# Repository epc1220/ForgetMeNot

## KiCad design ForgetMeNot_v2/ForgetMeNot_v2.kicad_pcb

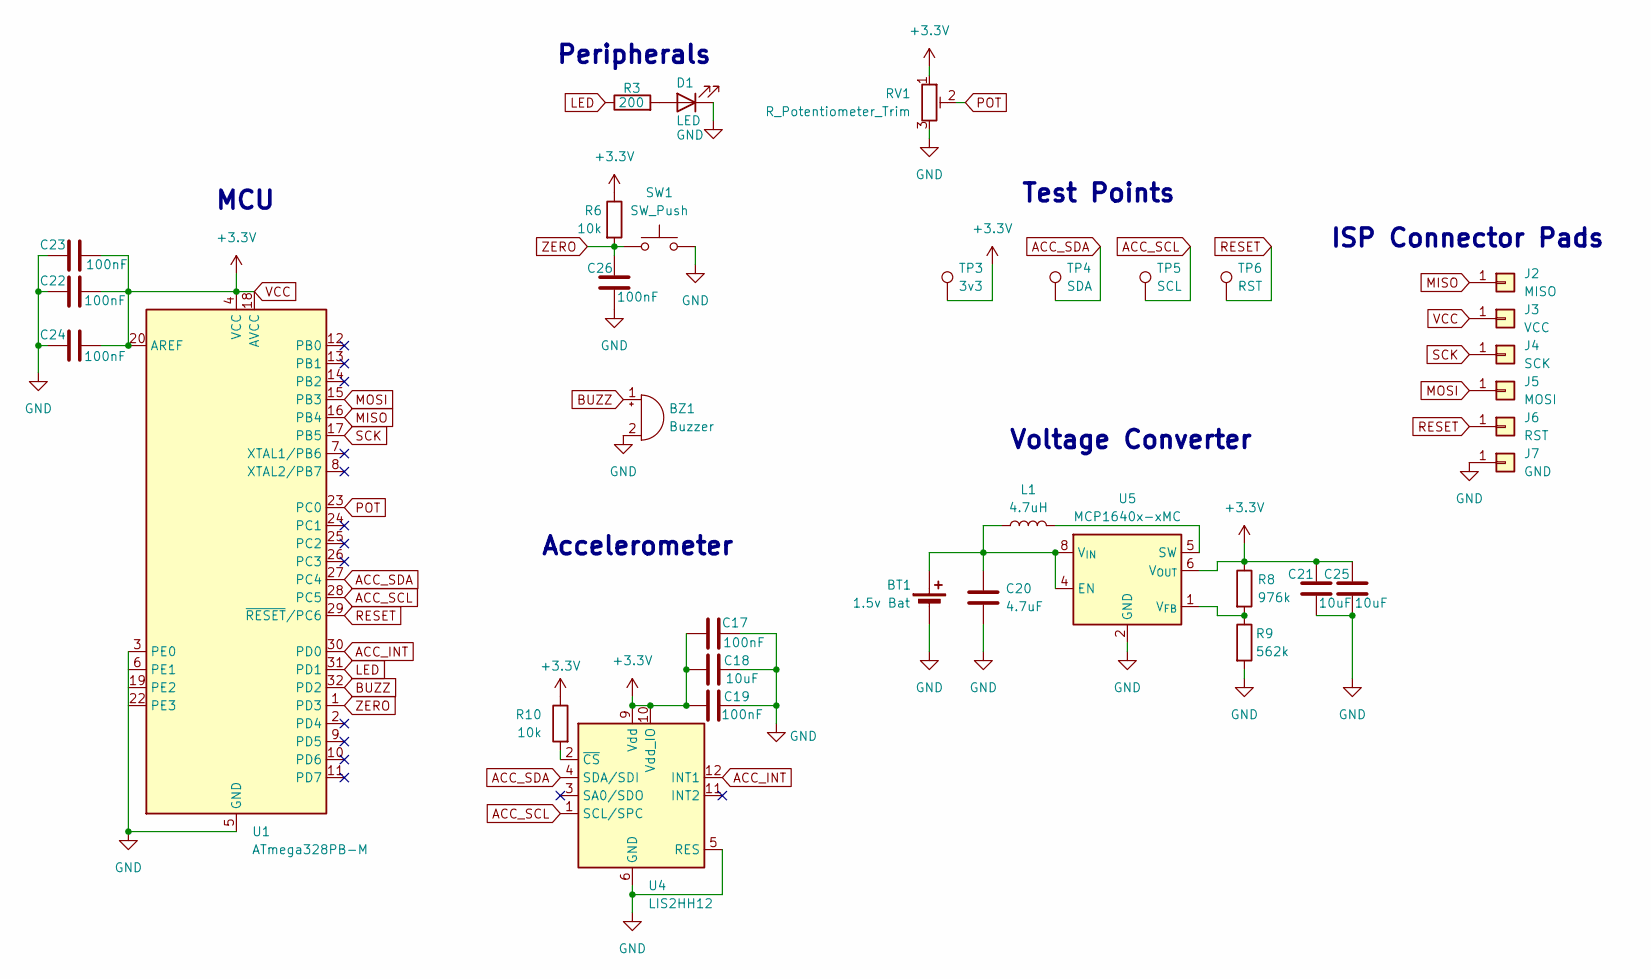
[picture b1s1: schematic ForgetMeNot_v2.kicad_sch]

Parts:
BT1: 1.5v Bat; BatteryHolder_Keystone_2998_1x6.8mm
BZ1: Buzzer; Buzzer_CUI_CPT-9019S-SMT
C17, C19, C22, C23, C24, C26: 100nF; C_0402_1005Metric
C18, C21, C25: 10uF; C_0402_1005Metric
C20: 4.7uF; C_0402_1005Metric
D1: LED; LED_0402_1005Metric
J2: MISO; SolderWirePad_1x01_SMD_3x6mm
J3: VCC; SolderWirePad_1x01_SMD_3x6mm
J4: SCK; SolderWirePad_1x01_SMD_3x6mm
J5: MOSI; SolderWirePad_1x01_SMD_3x6mm
J6: RST; SolderWirePad_1x01_SMD_3x6mm
J7: GND; SolderWirePad_1x01_SMD_3x6mm
L1: 4.7uH; L_1008_2520Metric
R3: 200; R_0402_1005Metric
R6, R10: 10k; R_0402_1005Metric
R8: 976k; R_0402_1005Metric
R9: 562k; R_0402_1005Metric
RV1: R_Potentiometer_Trim; Potentiometer_Bourns_TC33X_Vertical
SW1: SW_Push; SW_SPST_PTS810
TP3: 3v3; TestPoint_THTPad_D1.0mm_Drill0.5mm
TP4: SDA; TestPoint_THTPad_D1.0mm_Drill0.5mm
TP5: SCL; TestPoint_THTPad_D1.0mm_Drill0.5mm
TP6: RST; TestPoint_THTPad_D1.0mm_Drill0.5mm
U1: ATmega328PB-M; QFN-32-1EP_5x5mm_P0.5mm_EP3.1x3.1mm
U4: LIS2HH12; LGA-12_2x2mm_P0.5mm
U5: MCP1640x-xMC; DFN-8-1EP_3x2mm_P0.5mm_EP1.75x1.45mm

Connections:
ACC_INT: U1.30 (PD0), U4.12 (INT1)
ACC_SCL: TP5.1 (1_1), U1.28 (PC5), U4.1 (SCL/SPC)
ACC_SDA: TP4.1 (1_1), U1.27 (PC4), U4.4 (SDA/SDI)
BUZZ: BZ1.1 (+), U1.32 (PD2)
GND: BT1.2 (-), BZ1.2 (-), C17.1, C18.1, C19.1, C20.2, C21.1, C22.1, C23.1, C24.1, C25.1, C26.2, D1.1 (K), J7.1 (Pin_1_1), R9.2, RV1.3, SW1.2, U1.3 (GND), U1.5 (GND), U1.21 (GND), U1.33 (GND), U4.5 (RES), U4.6 (GND), U4.7 (GND), U4.8 (GND), U5.2 (GND), U5.3 (GND), U5.9 (GND)
LED: R3.1, U1.31 (PD1)
MISO: J2.1 (Pin_1_1), U1.16 (PB4)
MOSI: J5.1 (Pin_1_1), U1.15 (PB3)
unnamed: BT1.1 (+), C20.1, L1.1, U5.4 (EN), U5.8 (V_{IN})
unnamed: D1.2 (A), R3.2
unnamed: R10.2, U4.2 (~CS)
unnamed: L1.2, U5.5 (SW)
unnamed: R8.2, R9.1, U5.1 (V_{FB})
POT: RV1.2, U1.23 (PC0)
RESET: J6.1 (Pin_1_1), TP6.1 (1_1), U1.29 (~RESET/PC6)
SCK: J4.1 (Pin_1_1), U1.17 (PB5)
VCC: C17.2, C18.2, C19.2, C21.2, C22.2, C23.2, C24.2, C25.2, J3.1 (Pin_1_1), R6.1, R8.1, R10.1, RV1.1, TP3.1 (1_1), U1.4 (VCC), U1.6 (VCC), U1.18 (AVCC), U1.20 (AREF), U4.9 (Vdd), U4.10 (Vdd_IO), U5.6 (V_{OUT}), U5.7 (V_{OUT})
ZERO: C26.1, R6.2, SW1.1, U1.1 (PD3)

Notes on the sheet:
Test Points
ISP Connector Pads
Peripherals
Voltage Converter
Accelerometer
MCU

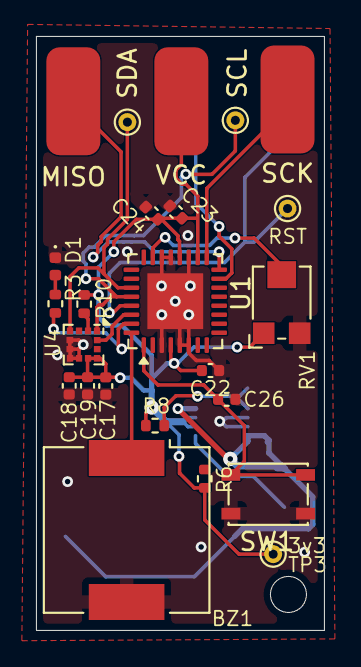
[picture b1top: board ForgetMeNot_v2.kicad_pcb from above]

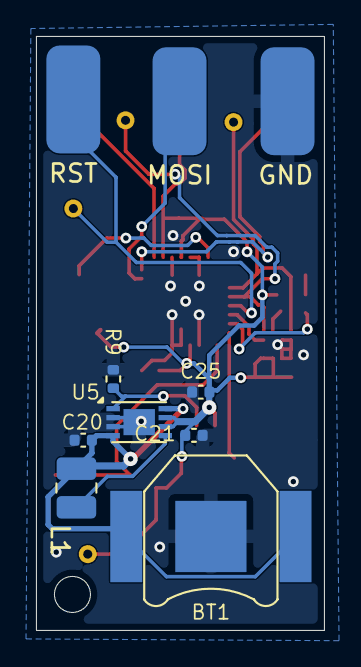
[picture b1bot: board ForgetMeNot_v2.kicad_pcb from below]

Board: 4 copper layers, 16.0 x 33.0 mm, 34 parts (10 on the bottom side), 18 nets.

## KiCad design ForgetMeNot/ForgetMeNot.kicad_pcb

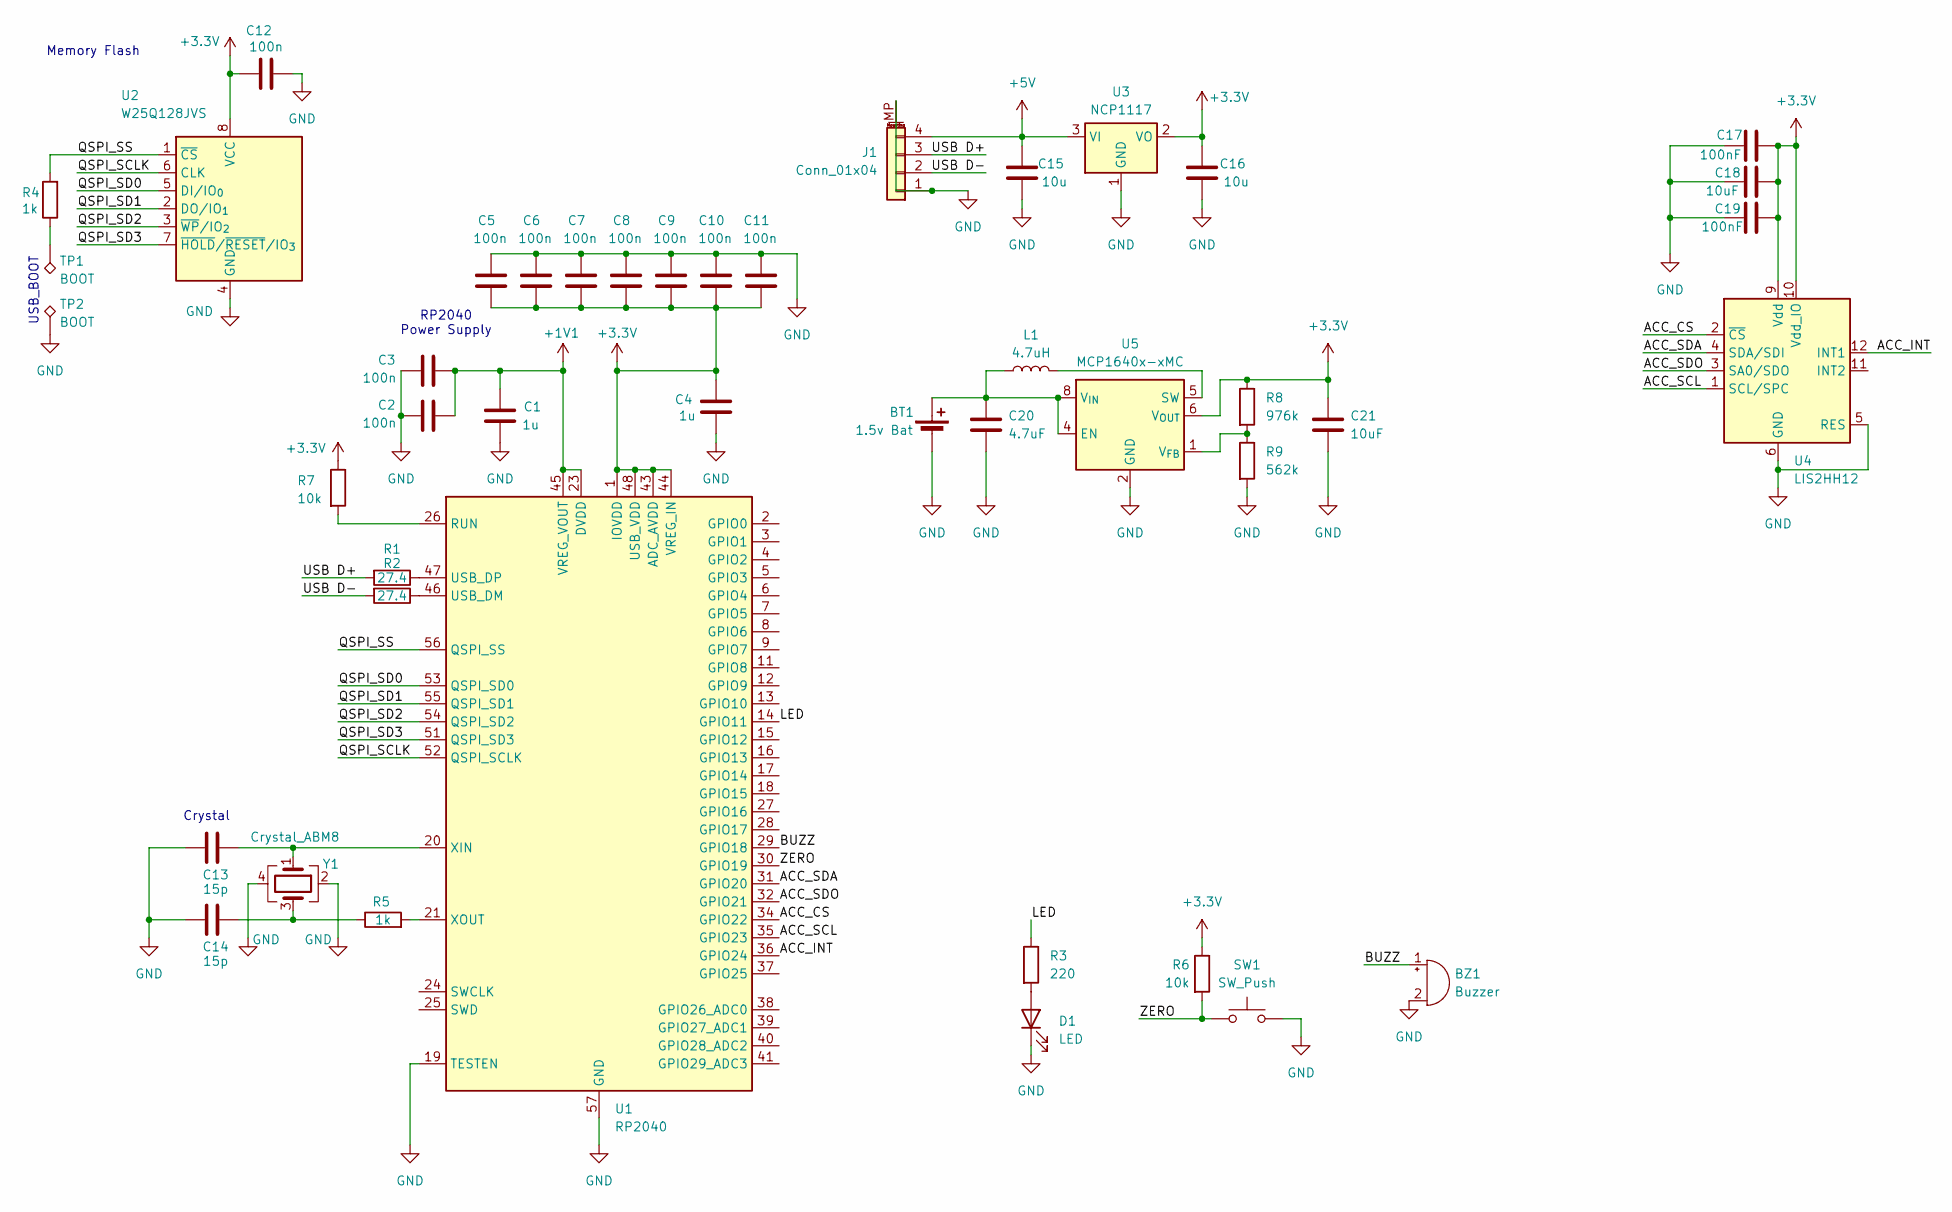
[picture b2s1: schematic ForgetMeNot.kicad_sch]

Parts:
BT1: 1.5v Bat; BatteryHolder_Keystone_2998_1x6.8mm
BZ1: Buzzer; Buzzer_CUI_CPT-9019S-SMT
C1, C4: 1u; C_0402_1005Metric
C2, C3, C5, C6, C7, C8, C9, C10, C11, C12: 100n; C_0402_1005Metric
C13, C14: 15p; C_0402_1005Metric
C15, C16: 10u; C_0402_1005Metric
C17, C19: 100nF; C_0402_1005Metric
C18, C21: 10uF; C_0402_1005Metric
C20: 4.7uF; C_0402_1005Metric
D1: LED; LED_0402_1005Metric
J1: Conn_01x04; Molex_CLIK-Mate_502585-0470_1x04-1MP_P1.50mm_Horizontal
L1: 4.7uH; L_0402_1005Metric
R1, R2: 27.4; R_0402_1005Metric
R3: 220; R_0402_1005Metric
R4, R5: 1k; R_0402_1005Metric
R6, R7: 10k; R_0402_1005Metric
R8: 976k; R_0402_1005Metric
R9: 562k; R_0402_1005Metric
SW1: SW_Push; SW_Push_1TS009xxxx-xxxx-xxxx_6x6x5mm
TP1, TP2: BOOT; TestPoint_THTPad_1.5x1.5mm_Drill0.7mm
U1: RP2040; QFN-56-1EP_7x7mm_P0.4mm_EP3.2x3.2mm
U2: W25Q128JVS; SOIC-8_5.3x5.3mm_P1.27mm
U3: NCP1117; SOT-223-3_TabPin2
U4: LIS2HH12; LGA-12_2x2mm_P0.5mm
U5: MCP1640x-xMC; DFN-8-1EP_3x2mm_P0.5mm_EP1.75x1.45mm
Y1: Crystal_ABM8; ABM8

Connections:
+1V1: C1.2, C2.2, C3.2, U1.23 (DVDD), U1.45 (VREG_VOUT), U1.50 (DVDD)
+3.3V: C4.2, C5.1, C6.1, C7.1, C8.1, C9.1, C10.1, C11.1, C12.1, C16.2, C17.2, C18.2, C19.2, C21.1, R6.1, R7.1, R8.1, U1.1 (IOVDD), U1.10 (IOVDD), U1.22 (IOVDD), U1.33 (IOVDD), U1.42 (IOVDD), U1.43 (ADC_AVDD), U1.44 (VREG_IN), U1.48 (USB_VDD), U1.49 (IOVDD), U2.8 (VCC), U3.2 (VO), U4.9 (Vdd), U4.10 (Vdd_IO), U5.6 (V_{OUT}), U5.7 (V_{OUT})
+5V: C15.2, J1.4, U3.3 (VI)
/ACC_CS: U1.34 (GPIO22), U4.2 (~CS)
/ACC_INT: U1.36 (GPIO24), U4.12 (INT1)
/ACC_SCL: U1.35 (GPIO23), U4.1 (SCL/SPC)
/ACC_SDA: U1.31 (GPIO20), U4.4 (SDA/SDI)
/ACC_SDO: U1.32 (GPIO21), U4.3 (SA0/SDO)
/BUZZ: BZ1.1 (+), U1.29 (GPIO18)
/LED: R3.1, U1.14 (GPIO11)
/QSPI_SCLK: U1.52 (QSPI_SCLK), U2.6 (CLK)
/QSPI_SD0: U1.53 (QSPI_SD0), U2.5 (DI/IO_{0})
/QSPI_SD1: U1.55 (QSPI_SD1), U2.2 (DO/IO_{1})
/QSPI_SD2: U1.54 (QSPI_SD2), U2.3 (~WP/IO_{2})
/QSPI_SD3: U1.51 (QSPI_SD3), U2.7 (~HOLD/~RESET/IO_{3})
/QSPI_SS: R4.2, U1.56 (QSPI_SS), U2.1 (~CS)
/USB D+: J1.3, R1.2
/USB D-: J1.2, R2.2
/ZERO: R6.2, SW1.1, U1.30 (GPIO19)
GND: BT1.2 (-), BZ1.2 (-), C1.1, C2.1, C3.1, C4.1, C5.2, C6.2, C7.2, C8.2, C9.2, C10.2, C11.2, C12.2, C13.1, C14.1, C15.1, C16.1, C17.1, C18.1, C19.1, C20.2, C21.2, D1.1 (K), J1.1, J1.MP (MountPin), R9.2, SW1.2, TP2.1, U1.19 (TESTEN), U1.57 (GND), U2.4 (GND), U3.1 (GND), U4.5 (RES), U4.6 (GND), U4.7 (GND), U4.8 (GND), U5.2 (GND), U5.3 (GND), U5.9 (GND), Y1.2, Y1.4
unnamed: BT1.1 (+), C20.1, L1.1, U5.4 (EN), U5.8 (V_{IN})
unnamed: C14.2, R5.1, Y1.3
unnamed: D1.2 (A), R3.2
unnamed: R4.1, TP1.1
unnamed: R7.2, U1.26 (RUN)
unnamed: R2.1, U1.46 (USB_DM)
unnamed: R1.1, U1.47 (USB_DP)
unnamed: C13.2, U1.20 (XIN), Y1.1
unnamed: R5.2, U1.21 (XOUT)
unnamed: L1.2, U5.5 (SW)
unnamed: R8.2, R9.1, U5.1 (V_{FB})

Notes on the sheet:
RP2040 Power Supply
Crystal
Memory Flash
USB_BOOT

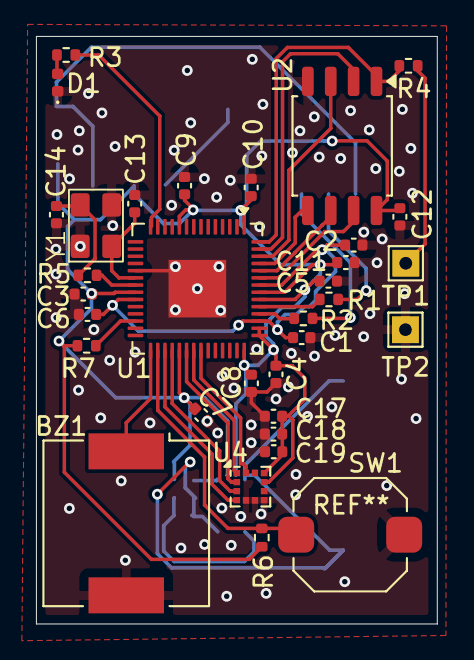
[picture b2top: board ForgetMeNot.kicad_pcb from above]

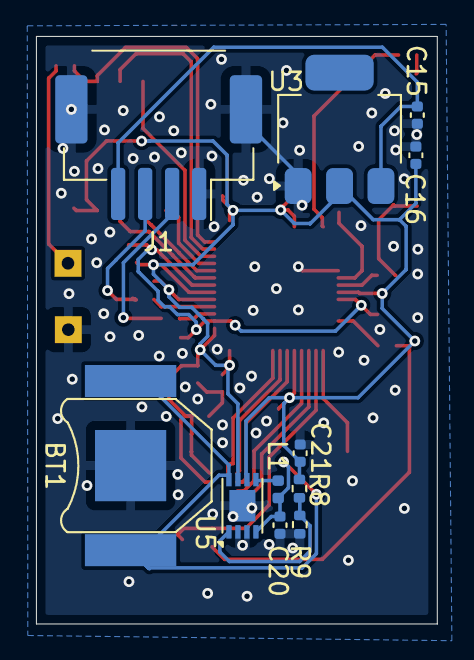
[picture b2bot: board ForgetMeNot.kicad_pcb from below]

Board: 4 copper layers, 22.3 x 32.6 mm, 44 parts (11 on the bottom side), 31 nets.

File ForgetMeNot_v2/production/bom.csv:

Designator,Footprint,Quantity,Value,LCSC Part #
BT1,BatteryHolder_Keystone_2998_1x6.8mm,1,1.5v Bat,
BZ1,Buzzer_CUI_CPT-9019S-SMT,1,Buzzer,
"C1, C4",0402,2,1u,
"C10, C11, C12, C2, C3, C5, C6, C7, C8, C9",0402,10,100n,
"C13, C14",0402,2,15p,
"C17, C19",0402,2,100nF,
"C18, C21",0402,2,10uF,
C20,0402,1,4.7uF,
D1,0402,1,LED,
J1,Molex_CLIK-Mate_502585-0470_1x04-1MP_P1.50mm_Horizontal,1,Conn_01x04,
L1,1008,1,4.7uH,
"R1, R2",0402,2,27.4,
R3,0402,1,220,
"R4, R5",0402,2,1k,
"R6, R7",0402,2,10k,
R8,0402,1,976k,
R9,0402,1,562k,
SW1,SW_SPST_PTS647_Sx38,1,SW_Push,
TP1,TestPoint_THTPad_1.0x1.0mm_Drill0.5mm,1,BOOT,
TP2,TestPoint_THTPad_D1.0mm_Drill0.5mm,1,BOOT,
TP3,TestPoint_THTPad_D1.0mm_Drill0.5mm,1,3v3,
TP4,TestPoint_Pad_D1.0mm,1,SDA,
TP5,TestPoint_Pad_D1.0mm,1,SCL,
U1,QFN-56-1EP_7x7mm_P0.4mm_EP3.2x3.2mm,1,RP2040,
U2,SOIC-8_5.3x5.3mm_P1.27mm,1,W25Q128JVS,
U4,LGA-12_2x2mm_P0.5mm,1,LIS2HH12,
U5,DFN-8-1EP_3x2mm_P0.5mm_EP1.75x1.45mm,1,MCP1640x-xMC,
Y1,ABM8,1,Crystal_ABM8,

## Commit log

2026-01-29 finished layout & tracing
2026-01-29 added more ground vias
2026-01-29 moved a resistor
2026-01-29 idk what i did but it wasnt significant
2026-01-29 Updated inductor
2026-01-31 removed ncp1117 so that the board is always powered by the battery and not the case of sometimes powered by the usb. (reduces complexity)
2026-02-03 test points
2026-02-03 added test points
2026-05-10 updated MCU from RP2040 to ATmega328p
2026-05-12 changed connector
2026-05-13 swapped connector for solder pads
